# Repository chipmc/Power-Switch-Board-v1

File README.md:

# Power-Switch-Board-v1
 Small board to support turning off power to i2c devices

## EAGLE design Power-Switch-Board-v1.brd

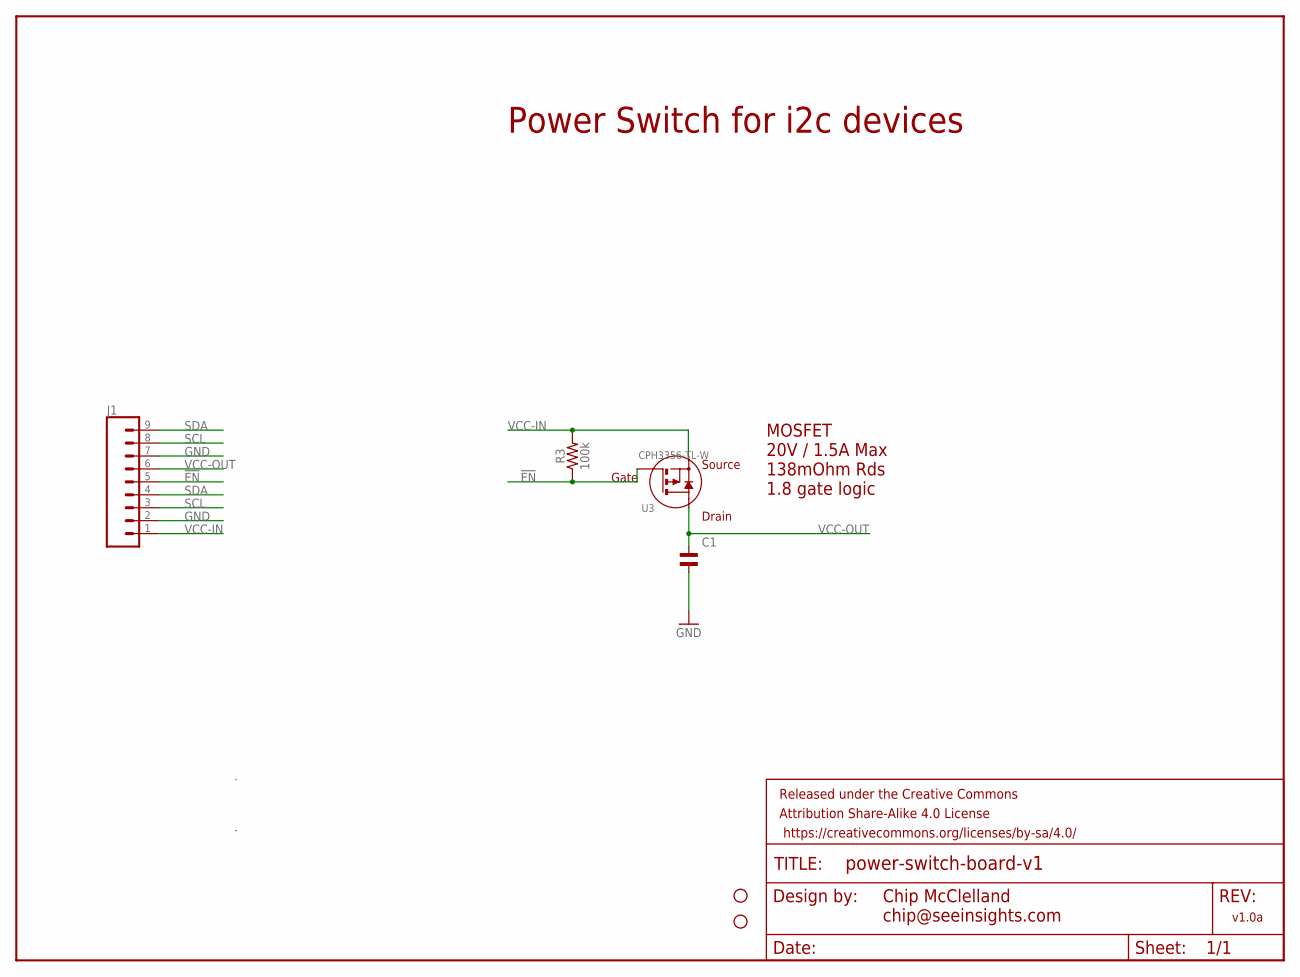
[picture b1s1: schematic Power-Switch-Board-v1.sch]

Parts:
C1: CAP-MF-0.1UF-; C0805
FRAME1: FRAME-LETTER; CREATIVE_COMMONS
H1, H2: STAND-OFF-M2.5
J1: CONN_09; 1X09
R3: 100k; 0805
U3: CPH3356-TL-W; SOT-23_ONS

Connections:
!EN: J1.5, R3.1, U3.1 (GATE)
GND: C1.P$2, J1.2, J1.7
SCL: J1.3, J1.8
SDA: J1.4, J1.9
VCC-IN: J1.1, R3.2, U3.2 (SOURCE)
VCC-OUT: C1.P$1, J1.6, U3.3 (DRAIN)

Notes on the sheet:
v1.0a
Chip McClelland chip@seeinsights.com
Power Switch for i2c devices
MOSFET 20V / 1.5A Max 138mOhm Rds 1.8 gate logic

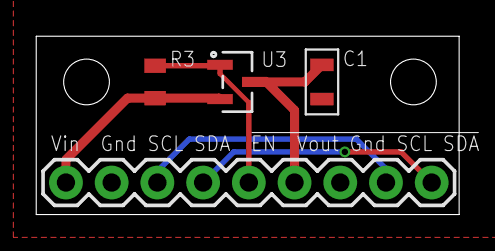
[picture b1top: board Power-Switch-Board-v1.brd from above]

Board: 2 copper layers, 23.5 x 9.9 mm, 7 parts (0 on the bottom side), 6 nets.

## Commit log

2021-12-11 typos
2021-12-14 Updated for 0.1" headers

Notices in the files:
parts and their libraries:
SparkFun-Aesthetics: Licensing: Creative Commons ShareAlike 4.0 International - https://creativecommons.org/licenses/by-sa/4.0
SparkFun-Aesthetics: Released under the Creative Commons Attribution Share-Alike 4.0 License
SparkFun-Aesthetics: https://creativecommons.org/licenses/by-sa/4.0
